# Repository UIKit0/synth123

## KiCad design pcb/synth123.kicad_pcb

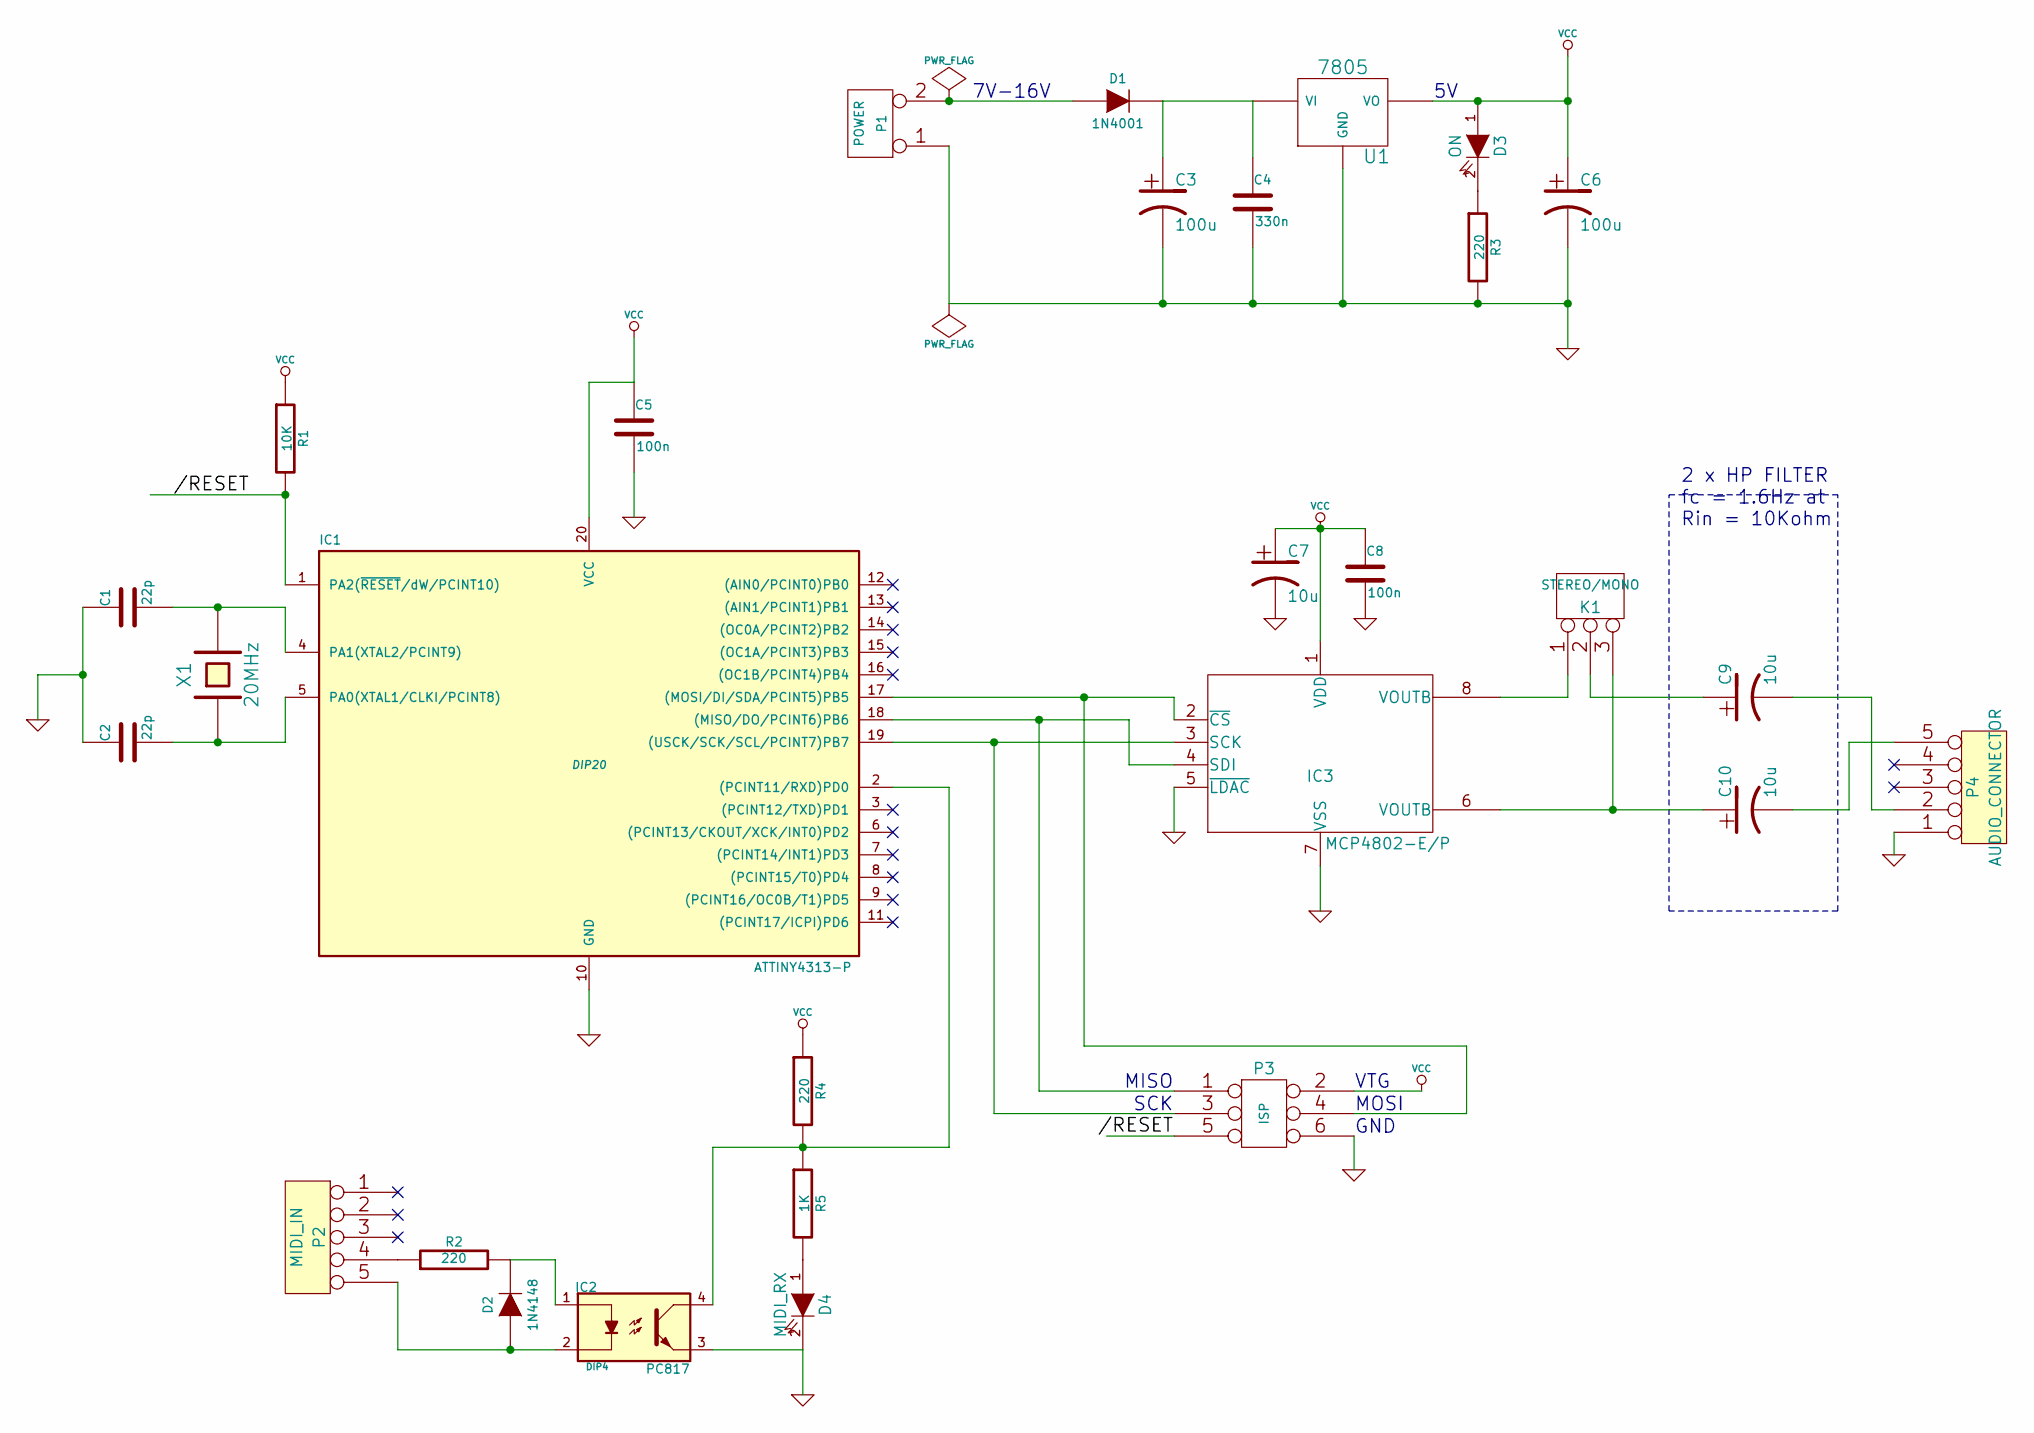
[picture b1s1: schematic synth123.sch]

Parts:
C1, C2: 22p
C3, C6: 100u
C4: 330n
C5, C8: 100n
C7, C9, C10: 10u
D1: 1N4001
D2: 1N4148
D3: ON
D4: MIDI_RX
IC1: ATTINY4313-P; DIP20
IC2: PC817; DIP4
IC3: MCP4802-E/P; DIP8
K1: STEREO/MONO
P1: POWER
P2: MIDI_IN
P3: ISP
P4: AUDIO_CONNECTOR
R1: 10K
R2, R3, R4: 220
R5: 1K
U1: 7805
X1: 20MHz

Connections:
//RESET: IC1.1 (PA2(~RESET~/dW/PCINT10)), P3.5, R1.2
GND: C1.1, C2.1, C3.2, C4.2, C5.2, C6.2, C7.2, C8.2, D4.2 (K), IC1.10 (GND), IC2.3, IC3.5 (~LDAC), IC3.7 (VSS), P1.1, P3.6, P4.1, R3.2, U1.GND
unnamed: IC1.17 ((MOSI/DI/SDA/PCINT5)PB5), IC3.2 (~CS), P3.4
unnamed: D2.2 (K), IC2.1, R2.2
unnamed: P2.4, R2.1
unnamed: D3.2 (K), R3.1
unnamed: IC3.8 (VOUTB), K1.1
unnamed: IC1.2 ((PCINT11/RXD)PD0), IC2.4, R4.2, R5.1
unnamed: D4.1 (A), R5.2
unnamed: C9.1, K1.2 (PM)
unnamed: C3.1, C4.1, D1.2 (K), U1.VI
unnamed: D1.1 (A), P1.2 (PM)
unnamed: C10.1, IC3.6 (VOUTB), K1.3
unnamed: C9.2, P4.2
unnamed: C10.2, P4.5
unnamed: IC1.19 ((USCK/SCK/SCL/PCINT7)PB7), IC3.3 (SCK), P3.3
unnamed: IC1.18 ((MISO/DO/PCINT6)PB6), IC3.4 (SDI), P3.1
unnamed: C2.2, IC1.5 (PA0(XTAL1/CLKI/PCINT8)), X1.1
unnamed: C1.2, IC1.4 (PA1(XTAL2/PCINT9)), X1.2
unnamed: D2.1 (A), IC2.2, P2.5
VCC: C5.1, C6.1, C7.1, C8.1, D3.1 (A), IC1.20 (VCC), IC3.1 (VDD), P3.2, R1.1, R4.1, U1.VO

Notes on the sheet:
MISO
SCK
VTG
MOSI
GND
7V-16V
2 x HP FILTER fc = 1.6Hz at Rin = 10Kohm

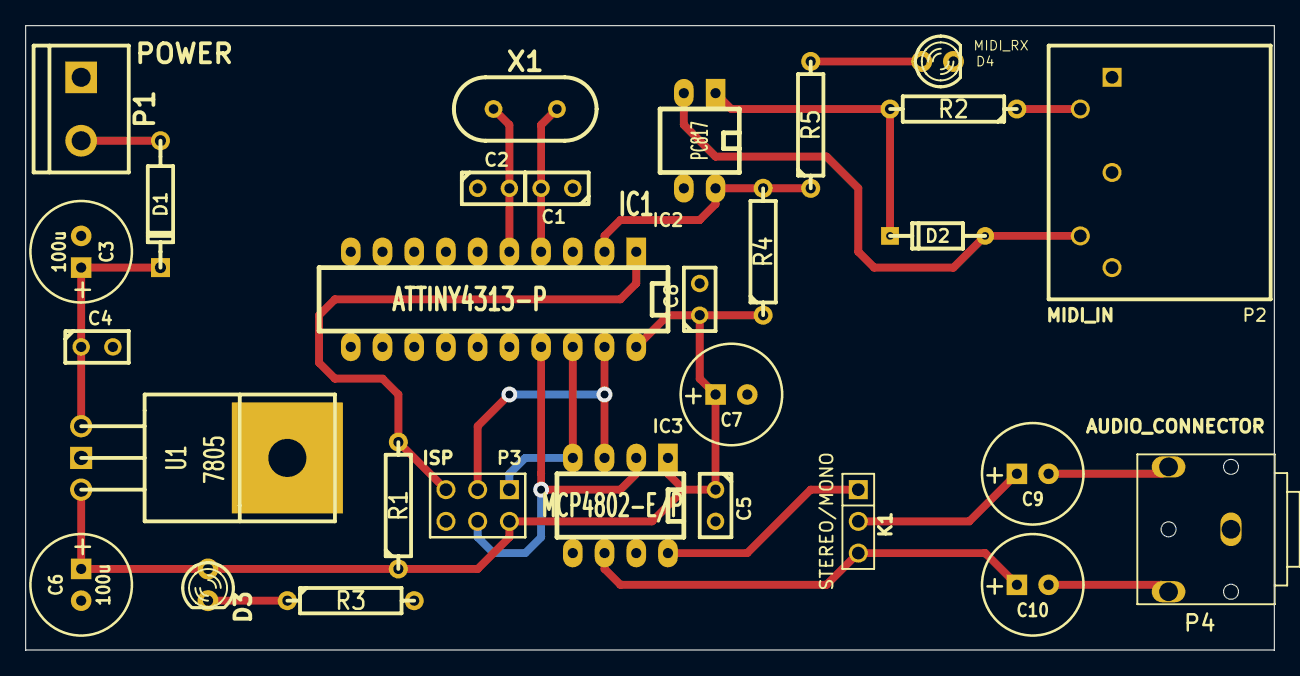
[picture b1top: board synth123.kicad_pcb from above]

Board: 2 copper layers, 100.0 x 50.0 mm, 29 parts (0 on the bottom side), 21 nets.

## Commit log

2013-05-04 Fast DAC writer, improved makefile
2013-05-05 Extended DAC API. Test code for UART.
2013-05-06 Restructured components.
2013-05-06 Added MIDI driver.
2013-05-10 Changed directory hierarchy.
2013-05-11 Added KiCAD schematic and PCB files.
2013-06-16 Updated KiCad files.
2013-06-16 Added DipTrace schematic.
2013-06-18 Patterns and schematic components.
2013-06-21 Created SOIC20 pattern.
2013-06-21 Created DIN5 and audio jack pattern.
2013-06-21 Schematic connections.
2013-06-21 SPI and ISP.
2013-06-21 Added 3d models. PCB Layout started.
2013-06-22 Compacted board
2013-06-22 Components placed.
2013-06-23 GND planes
2013-06-23 Board version 1.0
